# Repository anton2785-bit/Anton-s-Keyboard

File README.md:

# Anton-s-Keyboard
---

## What is this project

* This project is just a keyboard using 2 PCB layers. It has hotswapable switches and LEDs bellow every cap. The little oled screen will be used for brightens and lighting for the led. The rotary encoder will be volume controll. 
---
## Why i made this project
* My keyboard is starting to have some switches a little more squishi or lose compared to others. Also some of the keycaps are worn down.
* In conclusion I want to change my old keyboard with this one. 
---
# Schematic

* The shematic could be a little bit of a mess, but i had made it a month prior to this moment.

---
# PCB

* The PCB was redone 1 time, so that it was better with the lenght of traces and minimising the resistance.

---
# 3D case

* The case isnt perfect, but for now it will work. When i get all of the parts for the keyboard and then I will have the ability to measuer all of the things I need to make the case more percise. 

* Note: The case will be 3d printed by my friend and cost free. But I will maka corections on the case once i gen the whole thing and i have the propper dimensions for the holes and the usb cable going towards the Microcontroller. 

--- 
# Firmware
* The firmware will be changed once I get access to the microcontroller.
* The code now is generated by gemini. 
* 

--- 
# Assembly steps
* First the smaller parts must be souldered first because it will be harder to soulder the smaller components once the larger ones are placed / souldered.
* Secondly the larger components are souldered.
* Thirdly the foam is placed in the bottom case.
* After that all of the other parts are placed on the foam and closed off with the top plate.
* Finaly the cable can be connected to the PC and keyboard.

---
# BOM

| Component | Purpose | Qty | Cost (USD) | Distributor |
|-----------|---------|-----|------------|-------------|
| Gateron Stabilizers | Prevents larger keys from wobbling | 1 lot | $9.45 | Gateron |
| Capacitors 100nF | Noise decoupling for LEDs | 2 lots | $1.61 | AliExpress |
| 5V Level Shifter (74AHCT125) | Data line shifter for LEDs | 1 | $2.95 | AliExpress |
| LEDs (SK6812 Mini-E) | Per-key underglow LEDs | 2 lots | $3.56 | AliExpress |
| Keycaps | Keycaps | 1 set | $15.78 | AliExpress |
| Rotary Encoder (EC11E) | Volume/scroll knob | 1 | $2.78 | AliExpress |
| Diodes (1N4148W) | Prevent signal backflow in matrix | 2 lots | $1.84 | AliExpress |
| OLED Screen (0.91" 128x32) | Info display | 1 | $2.35 | AliExpress |
| Tantalum Capacitor (470µF 6.3V) | Bulk power decoupling for LEDs | 1 | $3.94 | AliExpress |
| Resistors (4.7kΩ and 350Ω) | Pull-up and current limiting | 1 pack | $4.10 | AliExpress |
| Foam | Sound dampening under PCB | 1 | $7.77 | AliExpress |
| Coiled Cable | Keyboard cable | 1 | $10.77 | AliExpress |
| PCB | Board fabrication | 1 | $51.00 | JLCPCB |
| Microcontroller (YD-RP2040) | Main controller | 1 | $2.94 | AliExpress |
| Gateron Switches | Mechanical switches | 1 set | $29.00 | Gateron |
| Hotswap Sockets | Easy switch swapping | 1 lot | $6.68 | Gateron |
| **Total** | | | **$156.52** | |

---
# Aditional notes on the design choices
* The bulk capacitors and the voltage regulator if for the data line going to the LEDs on the PCB.
* The case as mentioned above " will be 3d printed by my friend and cost free. But I will maka corections on the case once i gen the whole thing and i have the propper dimensions for the holes and the usb cable going towards the Microcontroller. "
--- 
# Credits

* Designed and built by (Anton/ Anton-2785-bit)
* Inspired by open‑source mechanical keyboard and hackpad communities (https://stasis.hackclub.com/dashboard).

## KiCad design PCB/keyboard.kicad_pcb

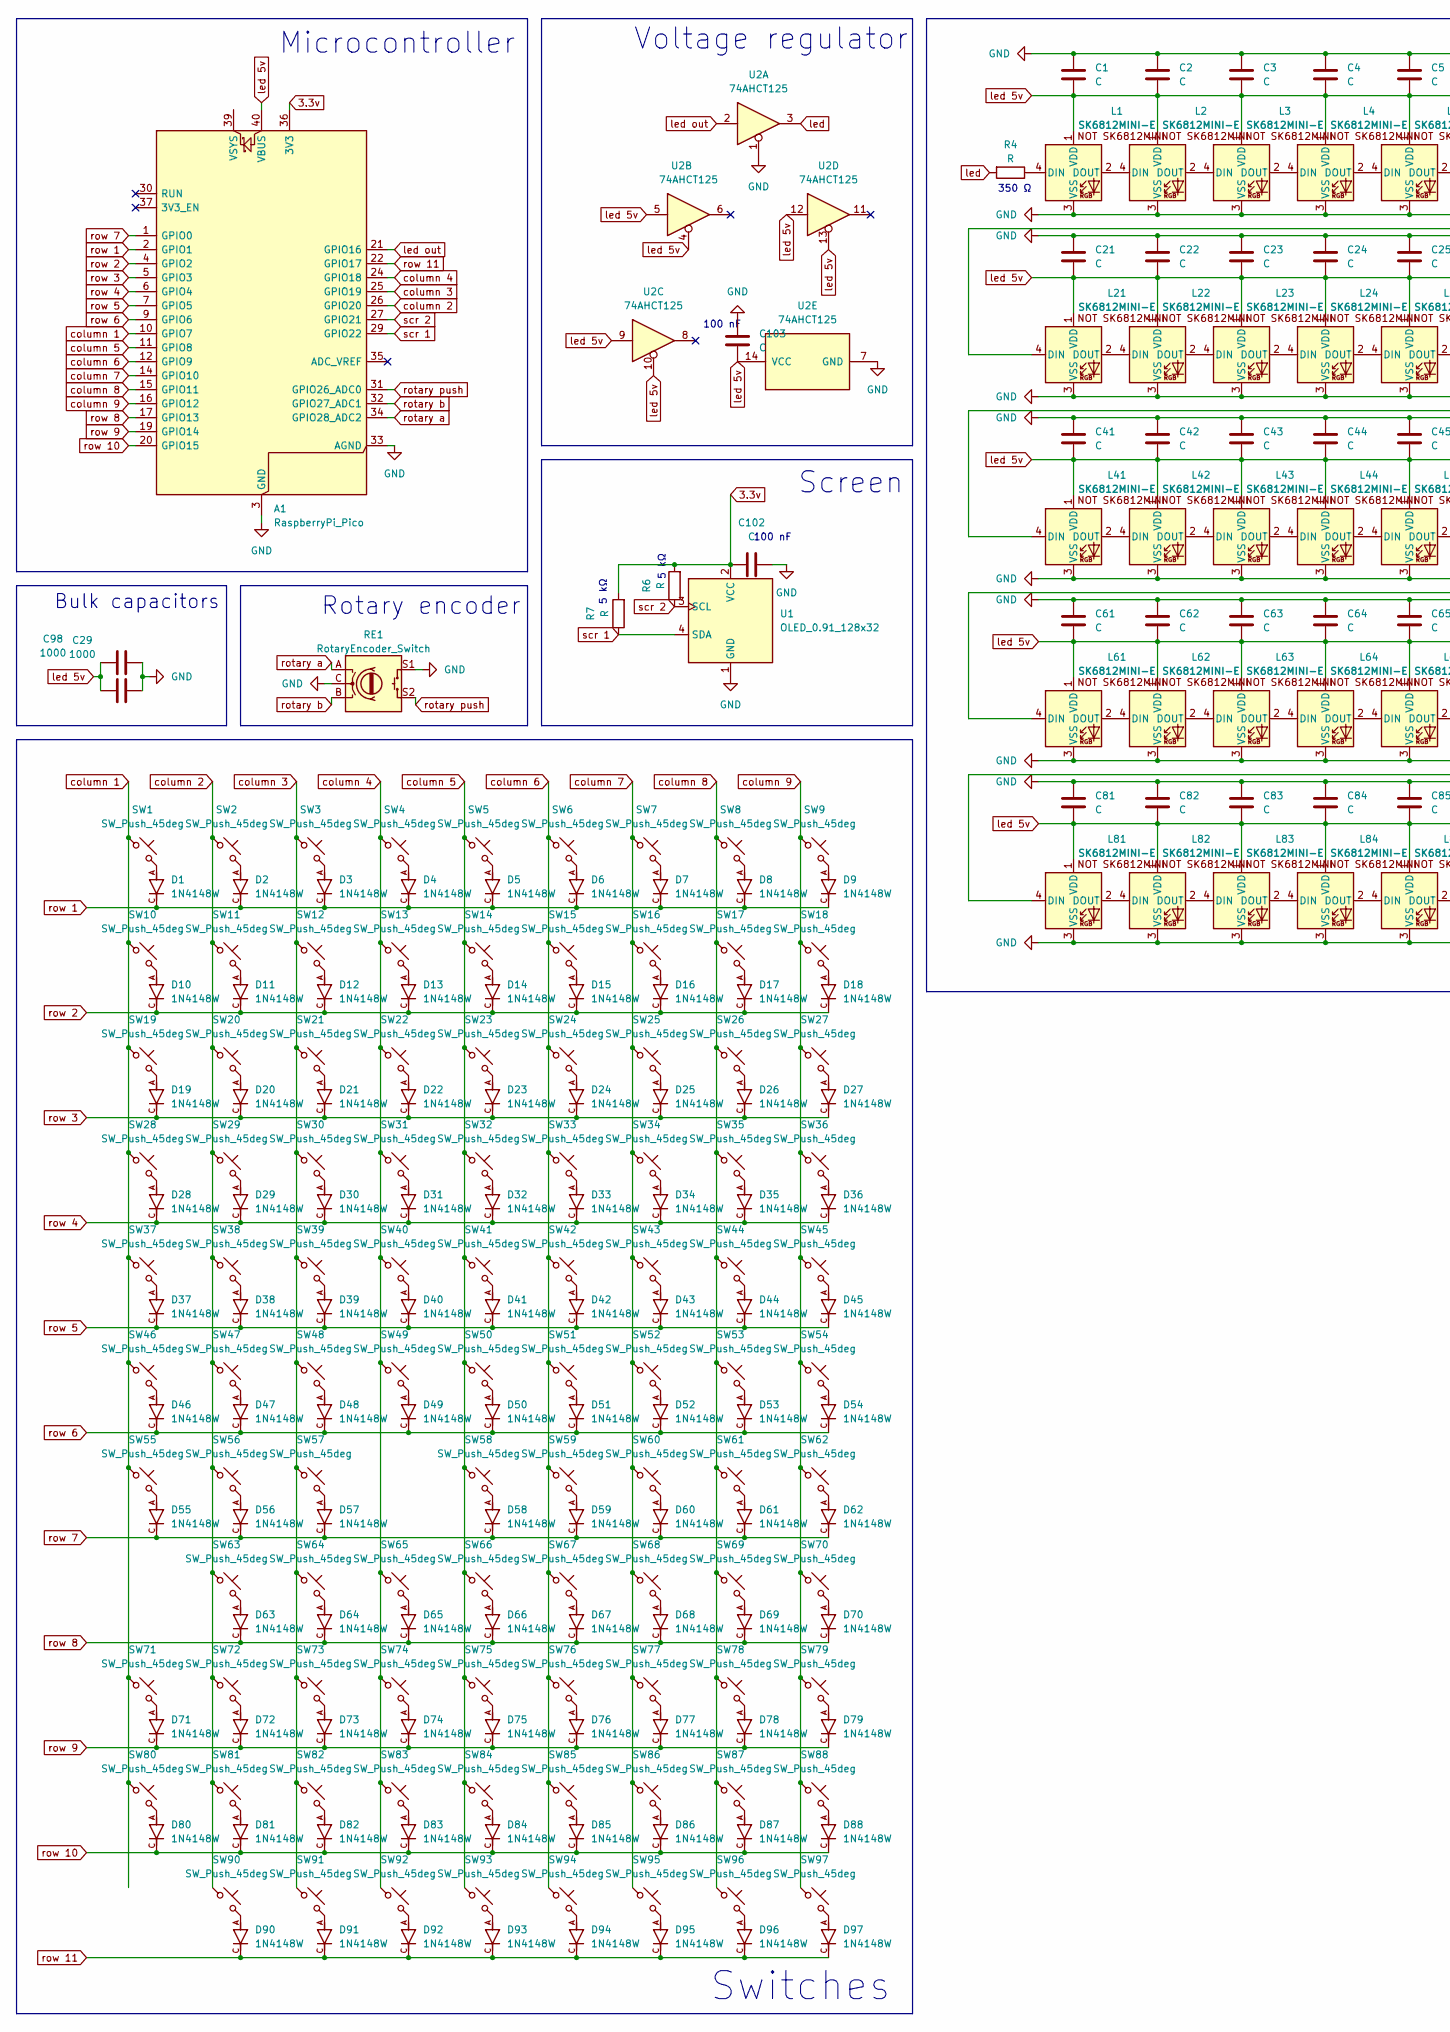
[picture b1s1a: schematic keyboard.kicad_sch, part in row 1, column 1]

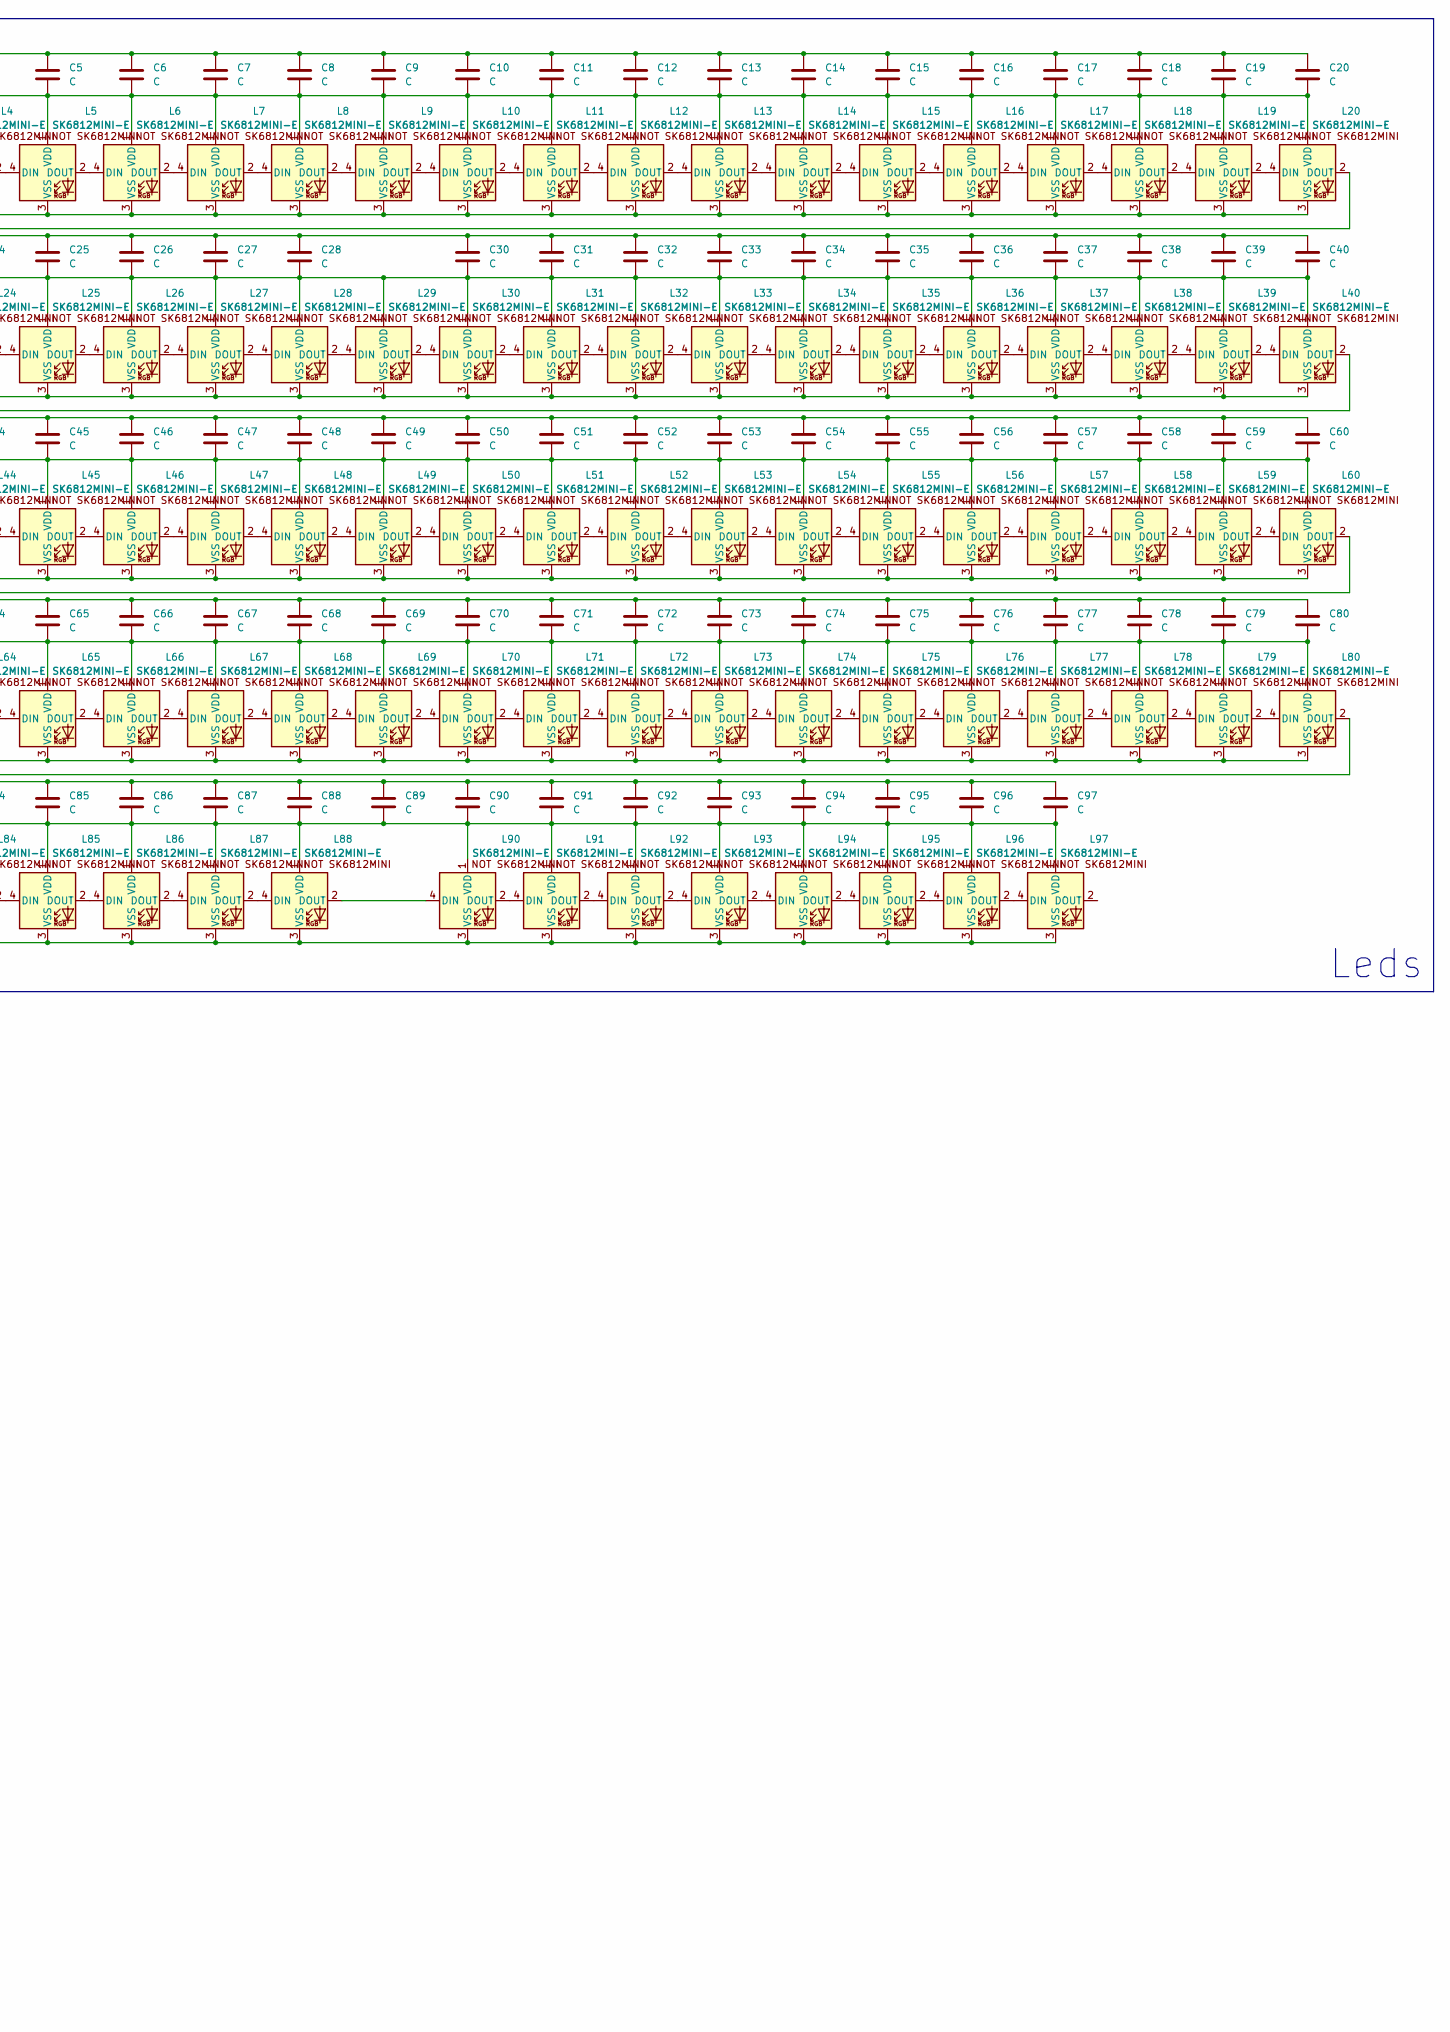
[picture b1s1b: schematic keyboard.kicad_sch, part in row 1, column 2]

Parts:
A1: RaspberryPi_Pico; RaspberryPi_Pico_SMD_HandSolder
C1, C2, C3, C4, C5, C6, C7, C8, C9, C10, C11, C12, C13, C14, C15, C16, C17, C18, C19, C20, C21, C22, C23, C24, C25, C26, C27, C28, C30, C31, C32, C33, C34, C35, C36, C37, C38, C39, C40, C41, C42, C43, C44, C45, C46, C47, C48, C49, C50, C51, C52, C53, C54, C55, C56, C57, C58, C59, C60, C61, C62, C63, C64, C65, C66, C67, C68, C69, C70, C71, C72, C73, C74, C75, C76, C77, C78, C79, C80, C81, C82, C83, C84, C85, C86, C87, C88, C89, C90, C91, C92, C93, C94, C95, C96, C97, C102, C103: C; C_0805_2012Metric_Pad1.18x1.45mm_HandSolder
C29, C98: 1000; CP_EIA-7343-31_Kemet-D_HandSolder
D1, D2, D3, D4, D5, D6, D7, D8, D9, D10, D11, D12, D13, D14, D15, D16, D17, D18, D19, D20, D21, D22, D23, D24, D25, D26, D27, D28, D29, D30, D31, D32, D33, D34, D35, D36, D37, D38, D39, D40, D41, D42, D43, D44, D45, D46, D47, D48, D49, D50, D51, D52, D53, D54, D55, D56, D57, D58, D59, D60, D61, D62, D63, D64, D65, D66, D67, D68, D69, D70, D71, D72, D73, D74, D75, D76, D77, D78, D79, D80, D81, D82, D83, D84, D85, D86, D87, D88, D90, D91, D92, D93, D94, D95, D96, D97: 1N4148W; SODFL3816X120N; PARTREV 2021-07-12
L1, L2, L3, L4, L5, L6, L7, L8, L9, L10, L11, L12, L13, L28, L29, L30, L31, L32, L33, L34, L35, L36, L37, L38, L39, L40, L41, L55, L56, L57, L58, L59, L60, L61, L62, L63, L64, L65, L66, L67, L68, L69, L70, L74, L75, L76, L80, L81: SK6812MINI-E; MX_sk6812_mini_e_v1
L14, L15, L16, L17, L18, L19, L20, L21, L22, L23, L24, L25, L26, L27, L42, L43, L44, L45, L46, L47, L48, L49, L50, L51, L52, L53, L54, L71, L72, L73, L77, L78, L79, L82, L83, L84, L85, L86, L87, L88, L90, L91, L92, L93, L94, L95, L96, L97: SK6812MINI-E; MX_sk6812_mini_e_v1_rotated
R4, R6, R7: R; R_0805_2012Metric_Pad1.20x1.40mm_HandSolder
RE1: RotaryEncoder_Switch; RotaryEncoder_Alps_EC11E-Switch_Vertical_H20mm_CircularMoun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
SW1, SW2, SW3, SW4, SW5, SW6, SW7, SW8, SW9, SW10, SW11, SW12, SW13, SW14, SW15, SW16, SW17, SW18, SW20, SW21, SW22, SW23, SW24, SW25, SW26, SW27, SW29, SW30, SW31, SW32, SW33, SW34, SW35, SW36, SW38, SW39, SW40, SW41, SW42, SW43, SW44, SW45, SW53, SW54, SW55, SW56, SW57, SW58, SW59, SW60, SW61, SW62, SW63, SW64, SW65, SW67, SW68, SW69, SW70, SW72, SW73, SW74, SW76, SW77, SW78, SW79, SW80, SW81, SW82, SW83, SW86, SW87, SW88, SW90, SW91, SW93, SW94, SW95, SW96, SW97: SW_Push_45deg; Hotswap_MX_1.00u
SW19, SW75: SW_Push_45deg; Hotswap_MX_1.50u
SW28, SW84: SW_Push_45deg; Hotswap_MX_1.75u
SW37, SW85: SW_Push_45deg; Hotswap_MX_2.25u
SW46, SW47, SW48, SW50, SW51, SW52: SW_Push_45deg; Hotswap_MX_1.25u
SW49: SW_Push_45deg; Hotswap_MX_6.25u
SW66: SW_Push_45deg; Hotswap_MX_2.00u
SW71, SW92: SW_Push_45deg; Hotswap_MX_2.00u_90deg
U1: OLED_0.91_128x32
U2: 74AHCT125; SOIC-14_3.9x8.7mm_P1.27mm

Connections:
3.3v: A1.36 (3V3), C102.2, R6.2, R7.2, U1.2 (VCC)
GND: A1.3 (GND), A1.8 (GND), A1.13 (GND), A1.18 (GND), A1.23 (GND), A1.28 (GND), A1.33 (AGND), A1.38 (GND), C1.2, C2.2, C3.2, C4.2, C5.2, C6.2, C7.2, C8.2, C9.2, C10.2, C11.2, C12.2, C13.2, C14.2, C15.2, C16.2, C17.2, C18.2, C19.2, C20.2, C21.2, C22.2, C23.2, C24.2, C25.2, C26.2, C27.2, C28.2, C29.2, C30.2, C31.2, C32.2, C33.2, C34.2, C35.2, C36.2, C37.2, C38.2, C39.2, C40.2, C41.2, C42.2, C43.2, C44.2, C45.2, C46.2, C47.2, C48.2, C49.2, C50.2, C51.2, C52.2, C53.2, C54.2, C55.2, C56.2, C57.2, C58.2, C59.2, C60.2, C61.2, C62.2, C63.2, C64.2, C65.2, C66.2, C67.2, C68.2, C69.2, C70.2, C71.2, C72.2, C73.2, C74.2, C75.2, C76.2, C77.2, C78.2, C79.2, C80.2, C81.2, C82.2, C83.2, C84.2, C85.2, C86.2, C87.2, C88.2, C89.2, C90.2, C91.2, C92.2, C93.2, C94.2, C95.2, C96.2, C97.2, C98.2, C102.1, C103.2, L1.3 (VSS), L2.3 (VSS), L3.3 (VSS), L4.3 (VSS), L5.3 (VSS), L6.3 (VSS), L7.3 (VSS), L8.3 (VSS), L9.3 (VSS), L10.3 (VSS), L11.3 (VSS), L12.3 (VSS), L13.3 (VSS), L14.3 (VSS), L15.3 (VSS), L16.3 (VSS), L17.3 (VSS), L18.3 (VSS), L19.3 (VSS), L20.3 (VSS), L21.3 (VSS), L22.3 (VSS), L23.3 (VSS), L24.3 (VSS), L25.3 (VSS), L26.3 (VSS), L27.3 (VSS), L28.3 (VSS), L29.3 (VSS), L30.3 (VSS), L31.3 (VSS), L32.3 (VSS), L33.3 (VSS), L34.3 (VSS), L35.3 (VSS), L36.3 (VSS), L37.3 (VSS), L38.3 (VSS), L39.3 (VSS), L40.3 (VSS), L41.3 (VSS), L42.3 (VSS), L43.3 (VSS), L44.3 (VSS), L45.3 (VSS), L46.3 (VSS), L47.3 (VSS), L48.3 (VSS), L49.3 (VSS), L50.3 (VSS), L51.3 (VSS), L52.3 (VSS), L53.3 (VSS), L54.3 (VSS), L55.3 (VSS), L56.3 (VSS), L57.3 (VSS), L58.3 (VSS), L59.3 (VSS), L60.3 (VSS), L61.3 (VSS), L62.3 (VSS), L63.3 (VSS), L64.3 (VSS), L65.3 (VSS), L66.3 (VSS), L67.3 (VSS), L68.3 (VSS), L69.3 (VSS), L70.3 (VSS), L71.3 (VSS), L72.3 (VSS), L73.3 (VSS), L74.3 (VSS), L75.3 (VSS), L76.3 (VSS), L77.3 (VSS), L78.3 (VSS), L79.3 (VSS), L80.3 (VSS), L81.3 (VSS), L82.3 (VSS), L83.3 (VSS), L84.3 (VSS), L85.3 (VSS), L86.3 (VSS), L87.3 (VSS), L88.3 (VSS), L90.3 (VSS), L91.3 (VSS), L92.3 (VSS), L93.3 (VSS), L94.3 (VSS), L95.3 (VSS), L96.3 (VSS), L97.3 (VSS), RE1.C, RE1.S1, U1.1 (GND), U2.1, U2.7 (GND)
unnamed: D1.A, SW1.2
unnamed: D2.A, SW2.2
unnamed: D3.A, SW3.2
unnamed: D4.A, SW4.2
unnamed: D5.A, SW5.2
unnamed: D6.A, SW6.2
unnamed: D7.A, SW7.2
unnamed: D8.A, SW8.2
unnamed: D9.A, SW9.2
unnamed: D10.A, SW10.2
unnamed: D11.A, SW11.2
unnamed: D12.A, SW12.2
unnamed: D13.A, SW13.2
unnamed: D14.A, SW14.2
unnamed: D15.A, SW15.2
unnamed: D16.A, SW16.2
unnamed: D17.A, SW17.2
unnamed: D18.A, SW18.2
unnamed: D19.A, SW19.2
unnamed: D20.A, SW20.2
unnamed: D21.A, SW21.2
unnamed: D22.A, SW22.2
unnamed: D23.A, SW23.2
unnamed: D24.A, SW24.2
unnamed: D25.A, SW25.2
unnamed: D26.A, SW26.2
unnamed: D27.A, SW27.2
unnamed: D28.A, SW28.2
unnamed: D29.A, SW29.2
unnamed: D30.A, SW30.2
unnamed: D31.A, SW31.2
unnamed: D32.A, SW32.2
unnamed: D33.A, SW33.2
unnamed: D34.A, SW34.2
unnamed: D35.A, SW35.2
unnamed: D36.A, SW36.2
unnamed: D37.A, SW37.2
unnamed: D38.A, SW38.2
unnamed: D39.A, SW39.2
unnamed: D40.A, SW40.2
unnamed: D41.A, SW41.2
unnamed: D42.A, SW42.2
unnamed: D43.A, SW43.2
unnamed: D44.A, SW44.2
unnamed: D45.A, SW45.2
unnamed: D46.A, SW46.2
unnamed: D47.A, SW47.2
unnamed: D48.A, SW48.2
unnamed: D49.A, SW49.2
unnamed: D50.A, SW50.2
unnamed: D51.A, SW51.2
unnamed: D52.A, SW52.2
unnamed: D53.A, SW53.2
unnamed: D54.A, SW54.2
unnamed: D55.A, SW55.2
unnamed: D56.A, SW56.2
unnamed: D57.A, SW57.2
unnamed: D58.A, SW58.2
unnamed: D59.A, SW59.2
unnamed: D60.A, SW60.2
unnamed: D61.A, SW61.2
unnamed: D62.A, SW62.2
unnamed: D63.A, SW63.2
unnamed: D64.A, SW64.2
unnamed: D65.A, SW65.2
unnamed: D66.A, SW66.2
unnamed: D67.A, SW67.2
unnamed: D68.A, SW68.2
unnamed: D69.A, SW69.2
unnamed: D70.A, SW70.2
unnamed: D71.A, SW71.2
unnamed: D72.A, SW72.2
unnamed: D73.A, SW73.2
unnamed: D74.A, SW74.2
unnamed: D75.A, SW75.2
unnamed: D76.A, SW76.2
unnamed: D77.A, SW77.2
unnamed: D78.A, SW78.2
unnamed: D79.A, SW79.2
unnamed: D80.A, SW80.2
unnamed: D81.A, SW81.2
unnamed: D82.A, SW82.2
unnamed: D83.A, SW83.2
unnamed: D84.A, SW84.2
unnamed: D85.A, SW85.2
unnamed: D86.A, SW86.2
unnamed: D87.A, SW87.2
unnamed: D88.A, SW88.2
unnamed: D90.A, SW90.2
unnamed: D91.A, SW91.2
unnamed: D92.A, SW92.2
unnamed: D93.A, SW93.2
unnamed: D94.A, SW94.2
unnamed: D95.A, SW95.2
unnamed: D96.A, SW96.2
unnamed: D97.A, SW97.2
unnamed: L1.4 (DIN), R4.1
unnamed: L1.2 (DOUT), L2.4 (DIN)
unnamed: L2.2 (DOUT), L3.4 (DIN)
unnamed: L3.2 (DOUT), L4.4 (DIN)
unnamed: L4.2 (DOUT), L5.4 (DIN)
unnamed: L5.2 (DOUT), L6.4 (DIN)
unnamed: L6.2 (DOUT), L7.4 (DIN)
unnamed: L7.2 (DOUT), L8.4 (DIN)
unnamed: L8.2 (DOUT), L9.4 (DIN)
unnamed: L9.2 (DOUT), L10.4 (DIN)
unnamed: L10.2 (DOUT), L11.4 (DIN)
unnamed: L11.2 (DOUT), L12.4 (DIN)
unnamed: L12.2 (DOUT), L13.4 (DIN)
unnamed: L13.2 (DOUT), L14.4 (DIN)
unnamed: L14.2 (DOUT), L15.4 (DIN)
unnamed: L15.2 (DOUT), L16.4 (DIN)
unnamed: L16.2 (DOUT), L17.4 (DIN)
unnamed: L17.2 (DOUT), L18.4 (DIN)
unnamed: L18.2 (DOUT), L19.4 (DIN)
unnamed: L19.2 (DOUT), L20.4 (DIN)
unnamed: L20.2 (DOUT), L21.4 (DIN)
unnamed: L21.2 (DOUT), L22.4 (DIN)
unnamed: L22.2 (DOUT), L23.4 (DIN)
unnamed: L23.2 (DOUT), L24.4 (DIN)
unnamed: L24.2 (DOUT), L25.4 (DIN)
unnamed: L25.2 (DOUT), L26.4 (DIN)
unnamed: L26.2 (DOUT), L27.4 (DIN)
unnamed: L27.2 (DOUT), L28.4 (DIN)
unnamed: L28.2 (DOUT), L29.4 (DIN)
unnamed: L29.2 (DOUT), L30.4 (DIN)
unnamed: L30.2 (DOUT), L31.4 (DIN)
unnamed: L31.2 (DOUT), L32.4 (DIN)
unnamed: L32.2 (DOUT), L33.4 (DIN)
unnamed: L33.2 (DOUT), L34.4 (DIN)
unnamed: L34.2 (DOUT), L35.4 (DIN)
unnamed: L35.2 (DOUT), L36.4 (DIN)
unnamed: L36.2 (DOUT), L37.4 (DIN)
unnamed: L37.2 (DOUT), L38.4 (DIN)
unnamed: L38.2 (DOUT), L39.4 (DIN)
unnamed: L39.2 (DOUT), L40.4 (DIN)
unnamed: L40.2 (DOUT), L41.4 (DIN)
unnamed: L41.2 (DOUT), L42.4 (DIN)
unnamed: L42.2 (DOUT), L43.4 (DIN)
unnamed: L43.2 (DOUT), L44.4 (DIN)
unnamed: L44.2 (DOUT), L45.4 (DIN)
unnamed: L45.2 (DOUT), L46.4 (DIN)
unnamed: L46.2 (DOUT), L47.4 (DIN)
unnamed: L47.2 (DOUT), L48.4 (DIN)
unnamed: L48.2 (DOUT), L49.4 (DIN)
unnamed: L49.2 (DOUT), L50.4 (DIN)
unnamed: L50.2 (DOUT), L51.4 (DIN)
unnamed: L51.2 (DOUT), L52.4 (DIN)
unnamed: L52.2 (DOUT), L53.4 (DIN)
unnamed: L53.2 (DOUT), L54.4 (DIN)
unnamed: L54.2 (DOUT), L55.4 (DIN)
unnamed: L55.2 (DOUT), L56.4 (DIN)
unnamed: L56.2 (DOUT), L57.4 (DIN)
unnamed: L57.2 (DOUT), L58.4 (DIN)
unnamed: L58.2 (DOUT), L59.4 (DIN)
unnamed: L59.2 (DOUT), L60.4 (DIN)
unnamed: L60.2 (DOUT), L61.4 (DIN)
unnamed: L61.2 (DOUT), L62.4 (DIN)
unnamed: L62.2 (DOUT), L63.4 (DIN)
unnamed: L63.2 (DOUT), L64.4 (DIN)
unnamed: L64.2 (DOUT), L65.4 (DIN)
unnamed: L65.2 (DOUT), L66.4 (DIN)
unnamed: L66.2 (DOUT), L67.4 (DIN)
unnamed: L67.2 (DOUT), L68.4 (DIN)
unnamed: L68.2 (DOUT), L69.4 (DIN)
unnamed: L69.2 (DOUT), L70.4 (DIN)
unnamed: L70.2 (DOUT), L71.4 (DIN)
unnamed: L71.2 (DOUT), L72.4 (DIN)
unnamed: L72.2 (DOUT), L73.4 (DIN)
unnamed: L73.2 (DOUT), L74.4 (DIN)
unnamed: L74.2 (DOUT), L75.4 (DIN)
unnamed: L75.2 (DOUT), L76.4 (DIN)
unnamed: L76.2 (DOUT), L77.4 (DIN)
unnamed: L77.2 (DOUT), L78.4 (DIN)
unnamed: L78.2 (DOUT), L79.4 (DIN)
unnamed: L79.2 (DOUT), L80.4 (DIN)
unnamed: L80.2 (DOUT), L81.4 (DIN)
unnamed: L81.2 (DOUT), L82.4 (DIN)
unnamed: L82.2 (DOUT), L83.4 (DIN)
unnamed: L83.2 (DOUT), L84.4 (DIN)
unnamed: L84.2 (DOUT), L85.4 (DIN)
unnamed: L85.2 (DOUT), L86.4 (DIN)
unnamed: L86.2 (DOUT), L87.4 (DIN)
unnamed: L87.2 (DOUT), L88.4 (DIN)
unnamed: L88.2 (DOUT), L90.4 (DIN)
unnamed: L90.2 (DOUT), L91.4 (DIN)
unnamed: L91.2 (DOUT), L92.4 (DIN)
unnamed: L92.2 (DOUT), L93.4 (DIN)
unnamed: L93.2 (DOUT), L94.4 (DIN)
unnamed: L94.2 (DOUT), L95.4 (DIN)
unnamed: L95.2 (DOUT), L96.4 (DIN)
unnamed: L96.2 (DOUT), L97.4 (DIN)
column 1: A1.10 (GPIO7), SW1.1, SW10.1, SW19.1, SW28.1, SW37.1, SW46.1, SW55.1, SW71.1, SW80.1
column 2: A1.26 (GPIO20), SW2.1, SW11.1, SW20.1, SW29.1, SW38.1, SW47.1, SW56.1, SW63.1, SW72.1, SW81.1, SW90.1
column 3: A1.25 (GPIO19), SW3.1, SW12.1, SW21.1, SW30.1, SW39.1, SW48.1, SW57.1, SW64.1, SW73.1, SW82.1, SW91.1
column 4: A1.24 (GPIO18), SW4.1, SW13.1, SW22.1, SW31.1, SW40.1, SW49.1, SW65.1, SW74.1, SW83.1, SW92.1
column 5: A1.11 (GPIO8), SW5.1, SW14.1, SW23.1, SW32.1, SW41.1, SW50.1, SW58.1, SW66.1, SW75.1, SW84.1, SW93.1
column 6: A1.12 (GPIO9), SW6.1, SW15.1, SW24.1, SW33.1, SW42.1, SW51.1, SW59.1, SW67.1, SW76.1, SW85.1, SW94.1
column 7: A1.14 (GPIO10), SW7.1, SW16.1, SW25.1, SW34.1, SW43.1, SW52.1, SW60.1, SW68.1, SW77.1, SW86.1, SW95.1
column 8: A1.15 (GPIO11), SW8.1, SW17.1, SW26.1, SW35.1, SW44.1, SW53.1, SW61.1, SW69.1, SW78.1, SW87.1, SW96.1
column 9: A1.16 (GPIO12), SW9.1, SW18.1, SW27.1, SW36.1, SW45.1, SW54.1, SW62.1, SW70.1, SW79.1, SW88.1, SW97.1
led: R4.2, U2.3
led 5v: A1.40 (VBUS), C1.1, C2.1, C3.1, C4.1, C5.1, C6.1, C7.1, C8.1, C9.1, C10.1, C11.1, C12.1, C13.1, C14.1, C15.1, C16.1, C17.1, C18.1, C19.1, C20.1, C21.1, C22.1, C23.1, C24.1, C25.1, C26.1, C27.1, C28.1, C29.1, C30.1, C31.1, C32.1, C33.1, C34.1, C35.1, C36.1, C37.1, C38.1, C39.1, C40.1, C41.1, C42.1, C43.1, C44.1, C45.1, C46.1, C47.1, C48.1, C49.1, C50.1, C51.1, C52.1, C53.1, C54.1, C55.1, C56.1, C57.1, C58.1, C59.1, C60.1, C61.1, C62.1, C63.1, C64.1, C65.1, C66.1, C67.1, C68.1, C69.1, C70.1, C71.1, C72.1, C73.1, C74.1, C75.1, C76.1, C77.1, C78.1, C79.1, C80.1, C81.1, C82.1, C83.1, C84.1, C85.1, C86.1, C87.1, C88.1, C89.1, C90.1, C91.1, C92.1, C93.1, C94.1, C95.1, C96.1, C97.1, C98.1, C103.1, L1.1 (VDD), L2.1 (VDD), L3.1 (VDD), L4.1 (VDD), L5.1 (VDD), L6.1 (VDD), L7.1 (VDD), L8.1 (VDD), L9.1 (VDD), L10.1 (VDD), L11.1 (VDD), L12.1 (VDD), L13.1 (VDD), L14.1 (VDD), L15.1 (VDD), L16.1 (VDD), L17.1 (VDD), L18.1 (VDD), L19.1 (VDD), L20.1 (VDD), L21.1 (VDD), L22.1 (VDD), L23.1 (VDD), L24.1 (VDD), L25.1 (VDD), L26.1 (VDD), L27.1 (VDD), L28.1 (VDD), L29.1 (VDD), L30.1 (VDD), L31.1 (VDD), L32.1 (VDD), L33.1 (VDD), L34.1 (VDD), L35.1 (VDD), L36.1 (VDD), L37.1 (VDD), L38.1 (VDD), L39.1 (VDD), L40.1 (VDD), L41.1 (VDD), L42.1 (VDD), L43.1 (VDD), L44.1 (VDD), L45.1 (VDD), L46.1 (VDD), L47.1 (VDD), L48.1 (VDD), L49.1 (VDD), L50.1 (VDD), L51.1 (VDD), L52.1 (VDD), L53.1 (VDD), L54.1 (VDD), L55.1 (VDD), L56.1 (VDD), L57.1 (VDD), L58.1 (VDD), L59.1 (VDD), L60.1 (VDD), L61.1 (VDD), L62.1 (VDD), L63.1 (VDD), L64.1 (VDD), L65.1 (VDD), L66.1 (VDD), L67.1 (VDD), L68.1 (VDD), L69.1 (VDD), L70.1 (VDD), L71.1 (VDD), L72.1 (VDD), L73.1 (VDD), L74.1 (VDD), L75.1 (VDD), L76.1 (VDD), L77.1 (VDD), L78.1 (VDD), L79.1 (VDD), L80.1 (VDD), L81.1 (VDD), L82.1 (VDD), L83.1 (VDD), L84.1 (VDD), L85.1 (VDD), L86.1 (VDD), L87.1 (VDD), L88.1 (VDD), L90.1 (VDD), L91.1 (VDD), L92.1 (VDD), L93.1 (VDD), L94.1 (VDD), L95.1 (VDD), L96.1 (VDD), L97.1 (VDD), U2.4, U2.5, U2.9, U2.10, U2.12, U2.13, U2.14 (VCC)
led out: A1.21 (GPIO16), U2.2
rotary a: A1.34 (GPIO28_ADC2), RE1.A
rotary b: A1.32 (GPIO27_ADC1), RE1.B
rotary push: A1.31 (GPIO26_ADC0), RE1.S2
row 1: A1.2 (GPIO1), D1.C, D2.C, D3.C, D4.C, D5.C, D6.C, D7.C, D8.C, D9.C
row 2: A1.4 (GPIO2), D10.C, D11.C, D12.C, D13.C, D14.C, D15.C, D16.C, D17.C, D18.C
row 3: A1.5 (GPIO3), D19.C, D20.C, D21.C, D22.C, D23.C, D24.C, D25.C, D26.C, D27.C
row 4: A1.6 (GPIO4), D28.C, D29.C, D30.C, D31.C, D32.C, D33.C, D34.C, D35.C, D36.C
row 5: A1.7 (GPIO5), D37.C, D38.C, D39.C, D40.C, D41.C, D42.C, D43.C, D44.C, D45.C
row 6: A1.9 (GPIO6), D46.C, D47.C, D48.C, D49.C, D50.C, D51.C, D52.C, D53.C, D54.C
row 7: A1.1 (GPIO0), D55.C, D56.C, D57.C, D58.C, D59.C, D60.C, D61.C, D62.C
row 8: A1.17 (GPIO13), D63.C, D64.C, D65.C, D66.C, D67.C, D68.C, D69.C, D70.C
row 9: A1.19 (GPIO14), D71.C, D72.C, D73.C, D74.C, D75.C, D76.C, D77.C, D78.C, D79.C
row 10: A1.20 (GPIO15), D80.C, D81.C, D82.C, D83.C, D84.C, D85.C, D86.C, D87.C, D88.C
row 11: A1.22 (GPIO17), D90.C, D91.C, D92.C, D93.C, D94.C, D95.C, D96.C, D97.C
scr 1: A1.29 (GPIO22), R7.1, U1.4 (SDA)
scr 2: A1.27 (GPIO21), R6.1, U1.3 (SCL)

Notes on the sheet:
Rotary encoder
Switches
Microcontroller
5 kΩ
100 nF
Bulk capacitors
Screen
Voltage regulator
Leds
350 Ω

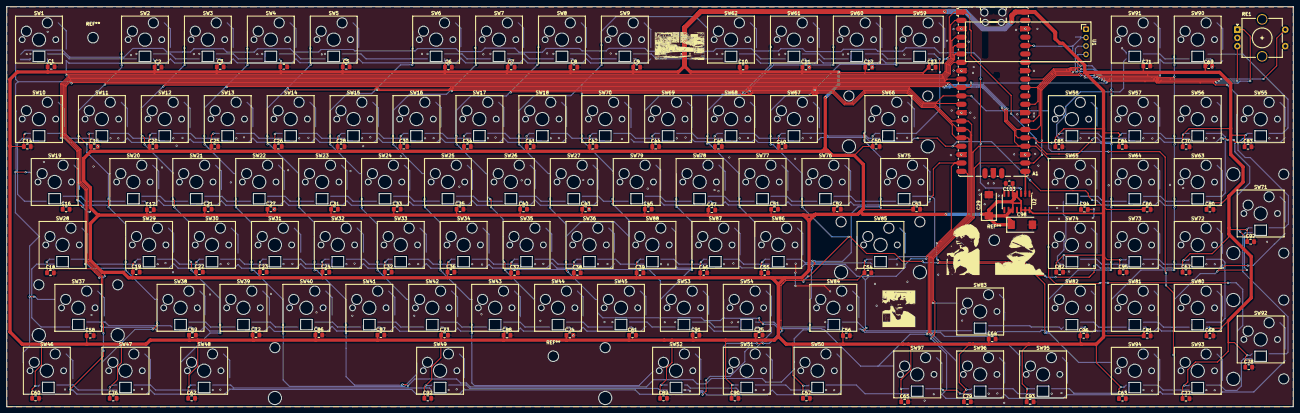
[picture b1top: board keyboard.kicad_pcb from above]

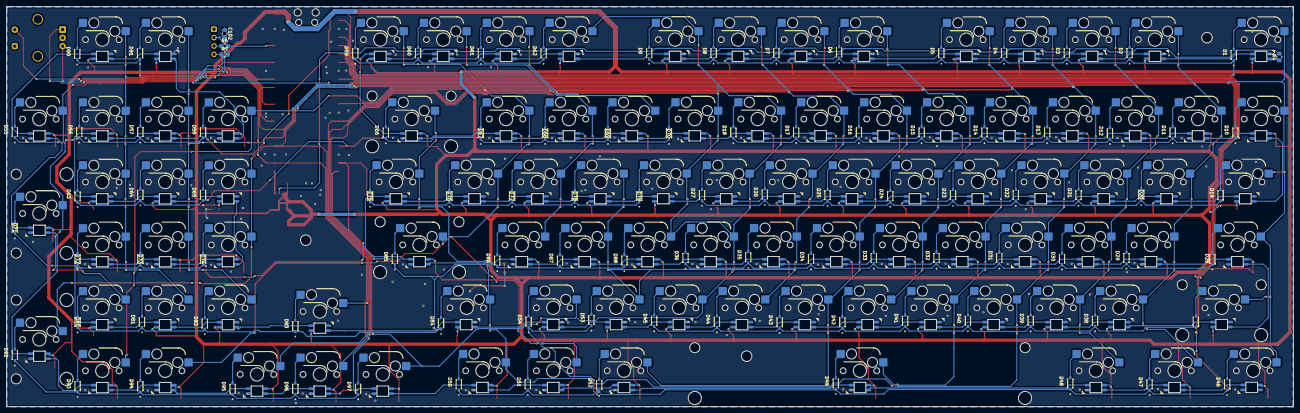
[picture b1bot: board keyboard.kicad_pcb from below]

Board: 2 copper layers, 389.6 x 121.1 mm, 395 parts (100 on the bottom side), 222 nets.

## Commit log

2026-02-28 File update
